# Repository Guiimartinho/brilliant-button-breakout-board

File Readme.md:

# Brilliant Button Breakout Board

See my blogpost for details: [https://p3dt.net/things/2019/10/04/brilliant-button-breakout-board.html](https://p3dt.net/things/2019/10/04/brilliant-button-breakout-board.html)

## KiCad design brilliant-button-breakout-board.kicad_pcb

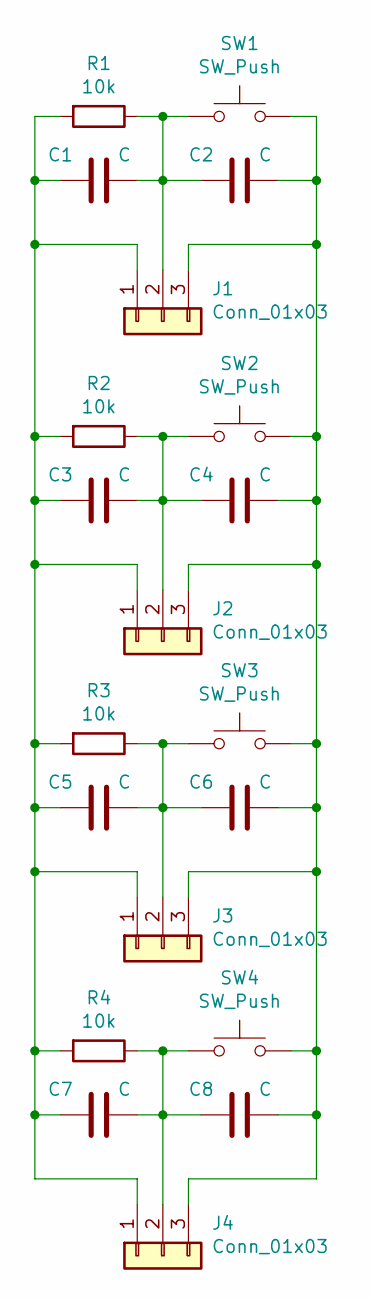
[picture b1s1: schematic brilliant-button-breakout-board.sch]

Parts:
C1, C2, C3, C4, C5, C6, C7, C8: C; C_0603_1608Metric_Pad1.05x0.95mm_HandSolder
J1, J2, J3, J4: Conn_01x03; PinHeader_1x03_P2.54mm_Vertical
R1, R2, R3, R4: 10k; R_0603_1608Metric_Pad1.05x0.95mm_HandSolder
SW1, SW2, SW3, SW4: SW_Push; SW_PUSH_6mm_H4.3mm

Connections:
unnamed: C1.1, C2.2, J1.2, R1.1, SW1.1
unnamed: C1.2, C3.2, C5.2, C7.2, J1.1, J2.1, J3.1, J4.1, R1.2, R2.2, R3.2, R4.2
unnamed: C2.1, C4.1, C6.1, C8.1, J1.3, J2.3, J3.3, J4.3, SW1.2, SW2.2, SW3.2, SW4.2
unnamed: C3.1, C4.2, J2.2, R2.1, SW2.1
unnamed: C5.1, C6.2, J3.2, R3.1, SW3.1
unnamed: C7.1, C8.2, J4.2, R4.1, SW4.1

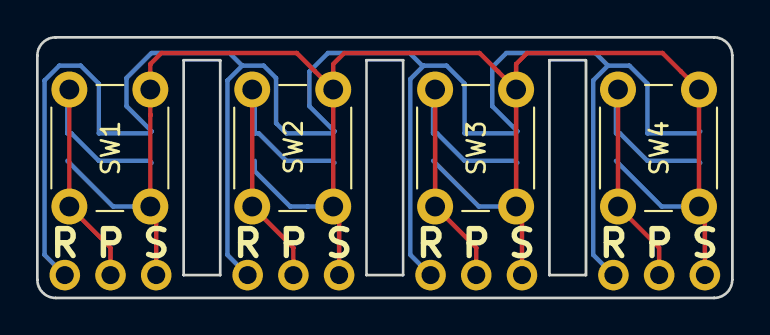
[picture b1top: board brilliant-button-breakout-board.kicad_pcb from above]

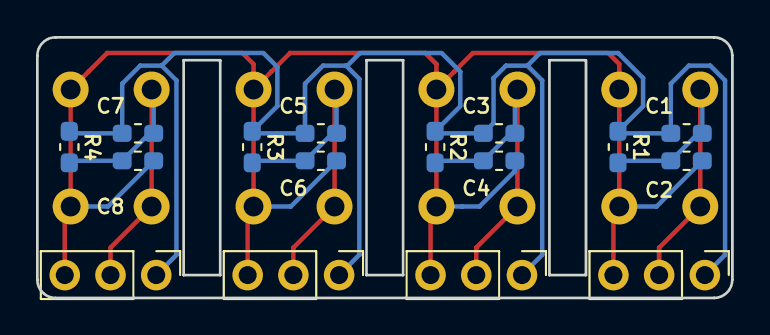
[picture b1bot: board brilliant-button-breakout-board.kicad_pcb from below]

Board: 2 copper layers, 38.6 x 14.5 mm, 20 parts (16 on the bottom side), 6 nets.

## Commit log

2019-10-04 add readme
2019-10-04 fix url
2019-10-05 capacitor update
